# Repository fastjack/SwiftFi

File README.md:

# SwiftFi
WiFi interface for Commodore 128D

This is an attempt at an internal WiFi modem for the Commodore 128D based on the SwiftLink cartridge as described in https://www.commodoreserver.com/BlogEntryView.asp?EID=FA5AE758474345A9A0A7208C7F408538

The PCB's dimensions were tailored for a C128D(DCR) mainboard since this is the only model of C128 I have available.

The PCB is sandwiched between U1 (CIA). Two additional signals need to be routed to this PCB. DOTCLK can be tapped from pin 6 on the expansion port. CS (chip select) can be tapped from (the unused) pin 16 of U3.

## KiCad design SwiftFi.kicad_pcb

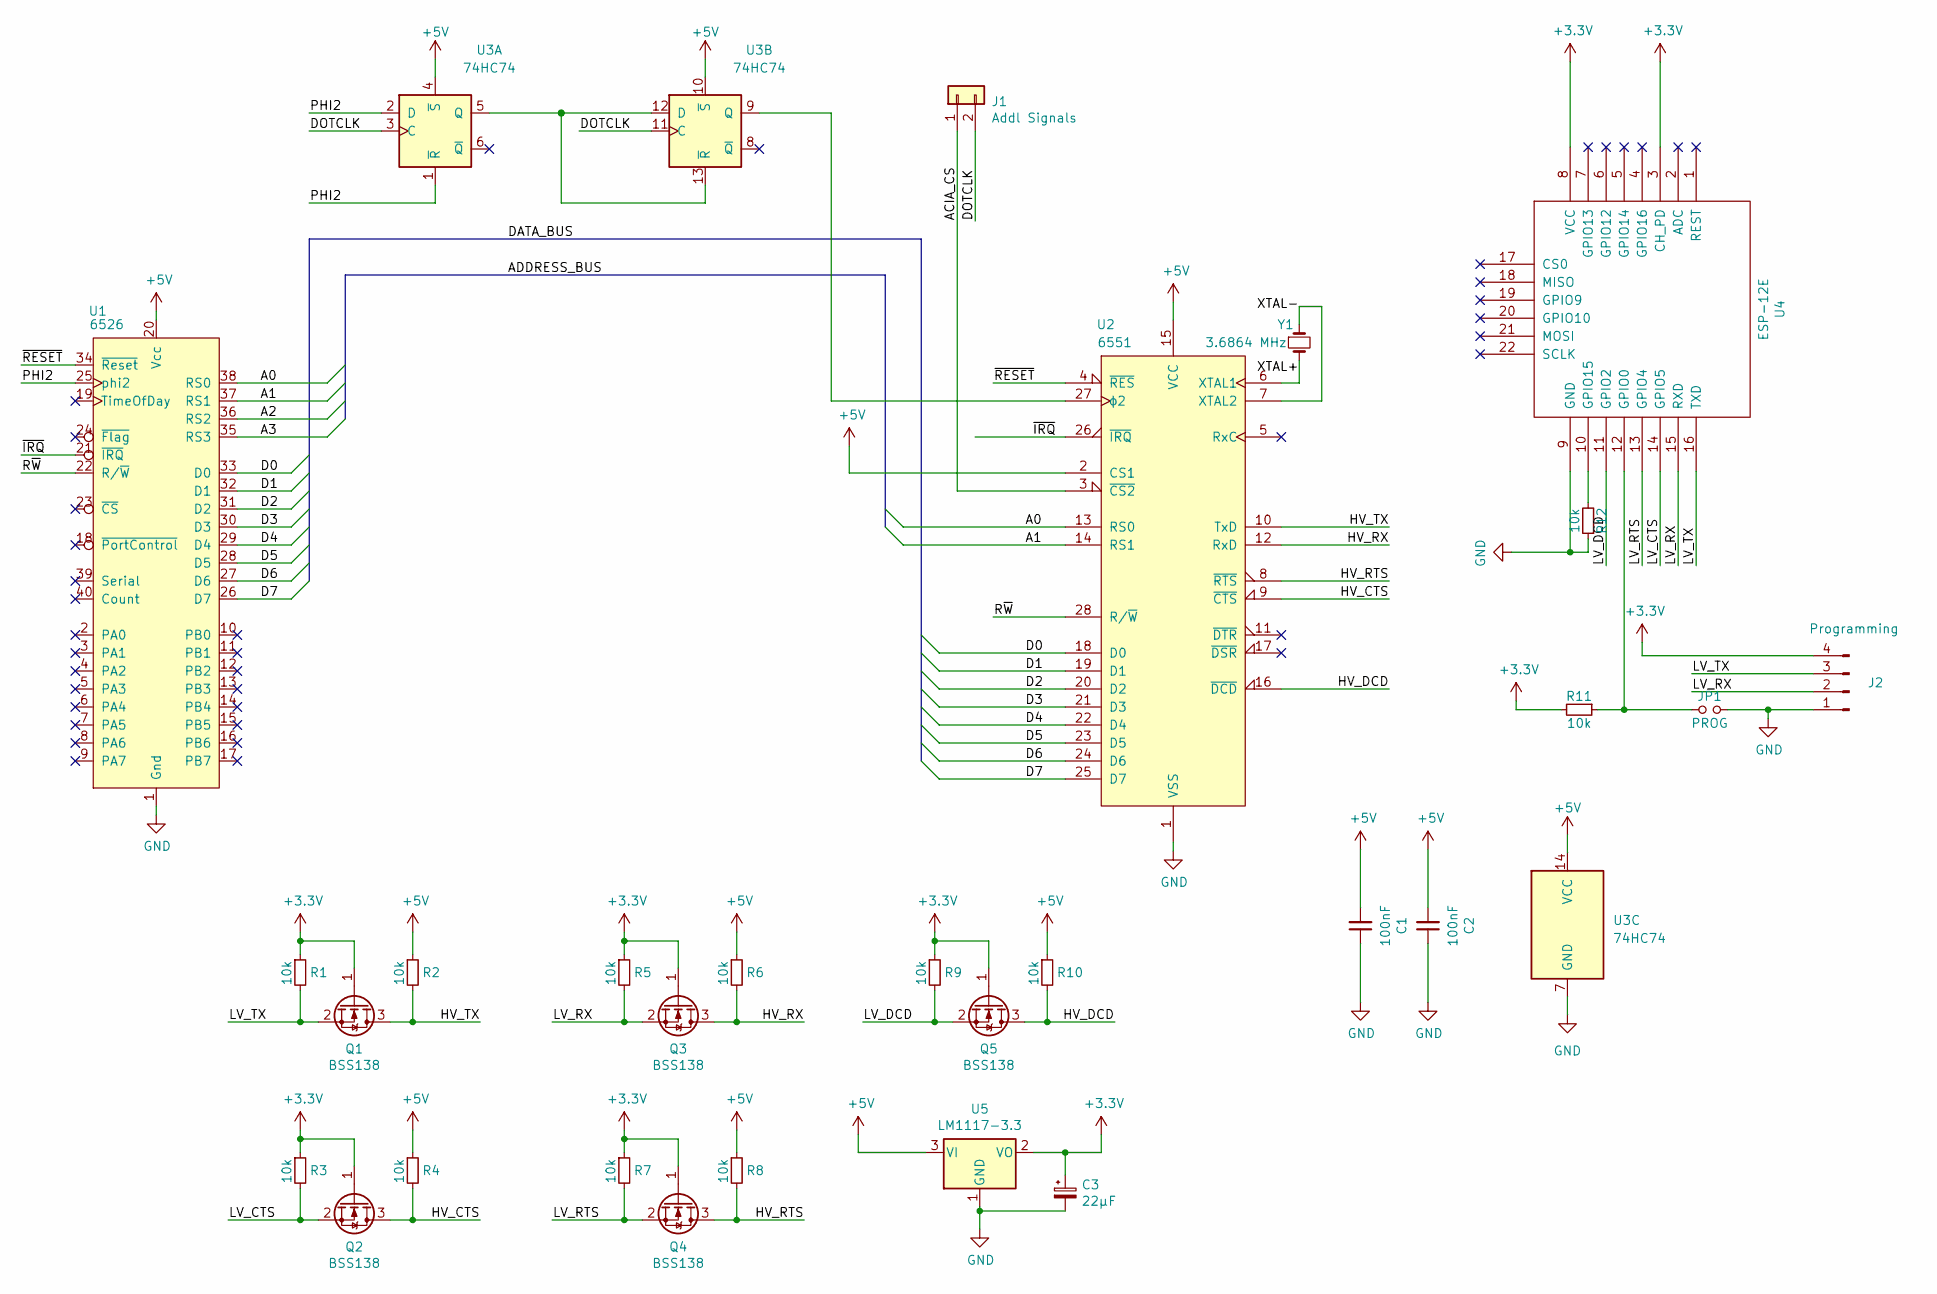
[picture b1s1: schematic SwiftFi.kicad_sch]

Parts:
C1, C2: 100nF; CP_EIA-3216-10_Kemet-I_Pad1.58x1.35mm_HandSolder; Digikey 478-8926-1-ND
C3: 22µF; CP_EIA-3216-10_Kemet-I_Pad1.58x1.35mm_HandSolder; Digikey 478-8429-1-ND
J1: Addl Signals; PinHeader_1x02_P2.54mm_Vertical; Digikey S1022E-02-ND
J2: Programming; PinHeader_1x04_P2.54mm_Vertical; Digikey S1222E-04-ND
JP1: PROG; PinHeader_1x02_P2.54mm_Vertical; Digikey S1022E-02-ND
Q1, Q2, Q3, Q4, Q5: BSS138; SOT-23; Digikey BSS138CT-ND
R1, R2, R3, R4, R5, R6, R7, R8, R9, R10, R11, R12: 10k; R_0603_1608Metric; Digikey 2368-SR1-0603-610-ND
U1: 6526; DIP-40_W15.24mm_Socket; Digikey ED3048-5-ND
U2: 6551; DIP-28_W15.24mm_Socket; Digikey 1175-1490-ND
U3: 74HC74; DIP-14_W7.62mm; Digikey 296-1602-5-ND
U4: ESP-12E; Digikey ESP-12SRF-ND
U5: LM1117-3.3; SOT-223; Digikey LM1117IMP-3.3/NOPBCT-ND
Y1: 3.6864 MHz; HC49%2fUS; Digikey XC1236CT-ND

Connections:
+3V3: C3.1, J2.4, Q1.1 (G), Q2.1 (G), Q3.1 (G), Q4.1 (G), Q5.1 (G), R1.1, R3.1, R5.1, R7.1, R9.1, R11.2, U4.3 (CH_PD), U4.8 (VCC), U5.2 (VO)
+5V: C1.2, C2.2, R2.1, R4.1, R6.1, R8.1, R10.1, U1.20 (Vcc), U2.2 (CS1), U2.15 (VCC), U3.4 (~S), U3.10 (~S), U3.14 (VCC), U5.3 (VI)
/A0: U1.38 (RS0), U2.13 (RS0)
/A1: U1.37 (RS1), U2.14 (RS1)
/A2: U1.36 (RS2)
/A3: U1.35 (RS3)
/ACIA_CS: J1.1, U2.3 (~CS2)
/D0: U1.33 (D0), U2.18 (D0)
/D1: U1.32 (D1), U2.19 (D1)
/D2: U1.31 (D2), U2.20 (D2)
/D3: U1.30 (D3), U2.21 (D3)
/D4: U1.29 (D4), U2.22 (D4)
/D5: U1.28 (D5), U2.23 (D5)
/D6: U1.27 (D6), U2.24 (D6)
/D7: U1.26 (D7), U2.25 (D7)
/DOTCLK: J1.2, U3.3 (C), U3.11 (C)
/HV_CTS: Q2.3 (D), R4.2, U2.9 (~CTS)
/HV_DCD: Q5.3 (D), R10.2, U2.16 (~DCD)
/HV_RTS: Q4.3 (D), R8.2, U2.8 (~RTS)
/HV_RX: Q3.3 (D), R6.2, U2.12 (RxD)
/HV_TX: Q1.3 (D), R2.2, U2.10 (TxD)
/LV_CTS: Q2.2 (S), R3.2, U4.14 (GPIO5)
/LV_DCD: Q5.2 (S), R9.2, U4.11 (GPIO2)
/LV_RTS: Q4.2 (S), R7.2, U4.13 (GPIO4)
/LV_RX: J2.2, Q3.2 (S), R5.2, U4.15 (RXD)
/LV_TX: J2.3, Q1.2 (S), R1.2, U4.16 (TXD)
/PHI2: U1.25 (phi2), U3.1 (~R), U3.2 (D)
/R~W: U1.22 (R/~W), U2.28 (R/~W)
/XTAL+: U2.6 (XTAL1), Y1.2
/XTAL-: U2.7 (XTAL2), Y1.1
/~IRQ: U1.21 (~IRQ), U2.26 (~IRQ)
/~RESET: U1.34 (~Reset), U2.4 (~RES)
GND: C1.1, C2.1, C3.2, J2.1, JP1.2, R12.1, U1.1 (Gnd), U2.1 (VSS), U3.7 (GND), U4.9 (GND), U5.1 (GND)
unnamed: JP1.1, R11.1, U4.12 (GPIO0)
unnamed: R12.2, U4.10 (GPIO15)
unnamed: U2.27 (ϕ2), U3.9 (Q)
unnamed: U3.5 (Q), U3.12 (D), U3.13 (~R)

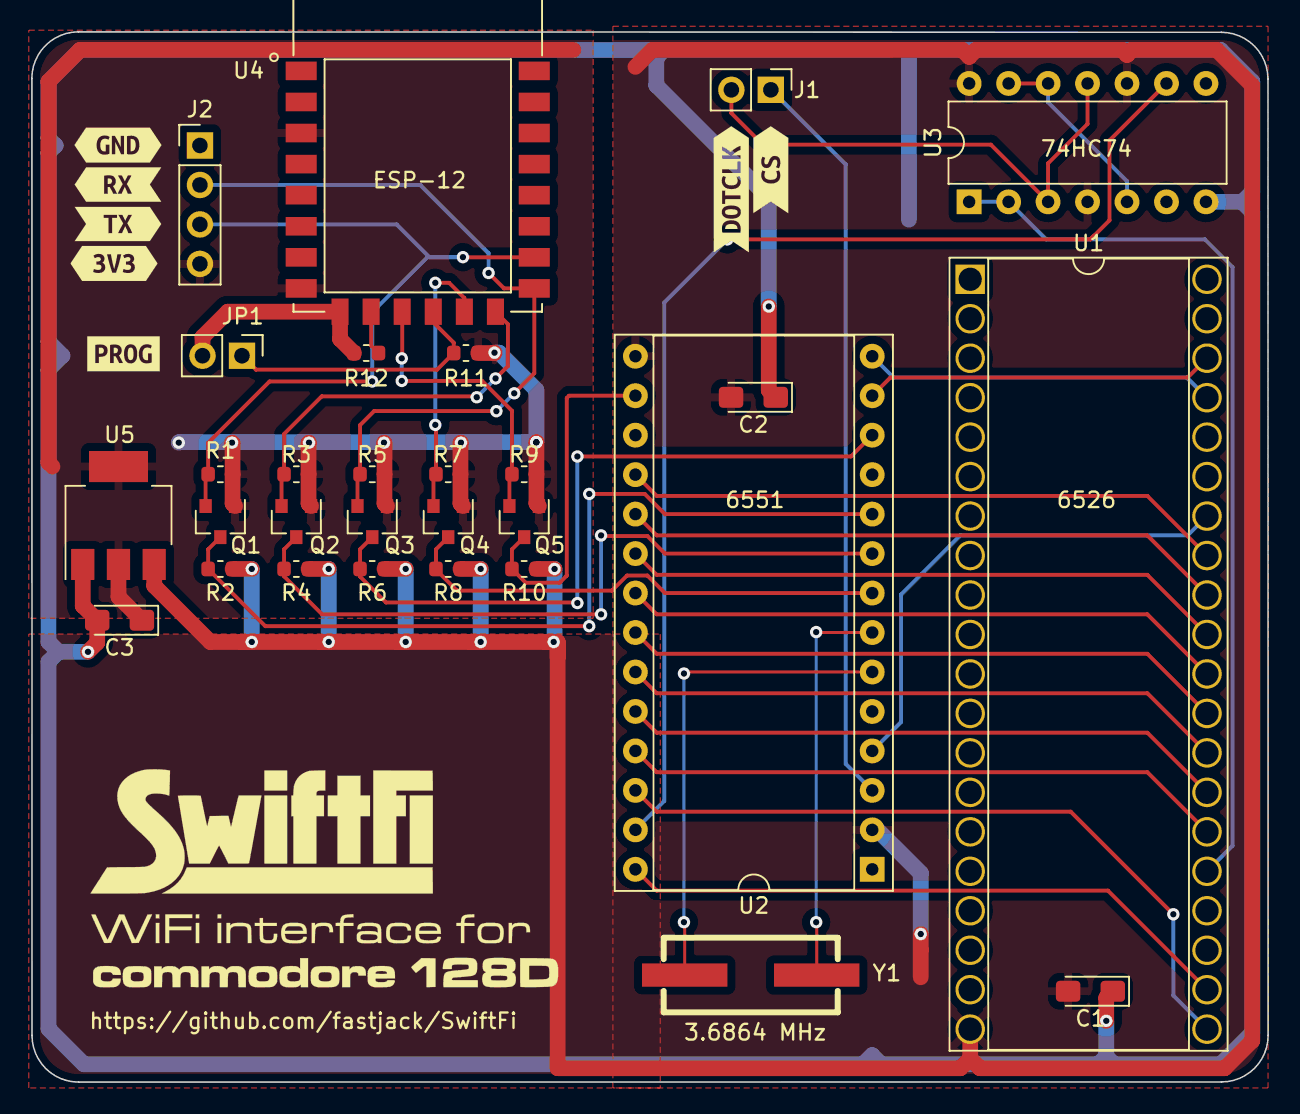
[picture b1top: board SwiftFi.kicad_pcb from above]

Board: 2 copper layers, 79.6 x 67.6 mm, 37 parts (0 on the bottom side), 35 nets.

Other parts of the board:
3V3_LABEL: G***; svg2mod
CS_LABEL: G***; svg2mod
DOTCLK_LABEL: G***; svg2mod
GND_LABEL: G***; svg2mod
PROG_LABEL: G***; svg2mod
RX_LABEL: G***; svg2mod
Ref**: Val**; SwiftFi 8mm
TX_LABEL: G***; svg2mod

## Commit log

2021-05-17 Added GitHub repo URL to PCB silkscreen
2021-05-17 changed footprints caps, added llinks to aliexpress in BOM
2021-05-24 Updated design rules to those recommended by OSHPark
    https://docs.oshpark.com/design-tools/kicad/kicad-design-rules/
2021-05-24 ignore overlapping courtyards of bypass caps inside DIP sockets
2021-05-24 enlarged drill holes for pins of CIA
    the individual pins intended to be used here require drill holes of 1.5 mm in diameter
2021-07-21 Updated logo
